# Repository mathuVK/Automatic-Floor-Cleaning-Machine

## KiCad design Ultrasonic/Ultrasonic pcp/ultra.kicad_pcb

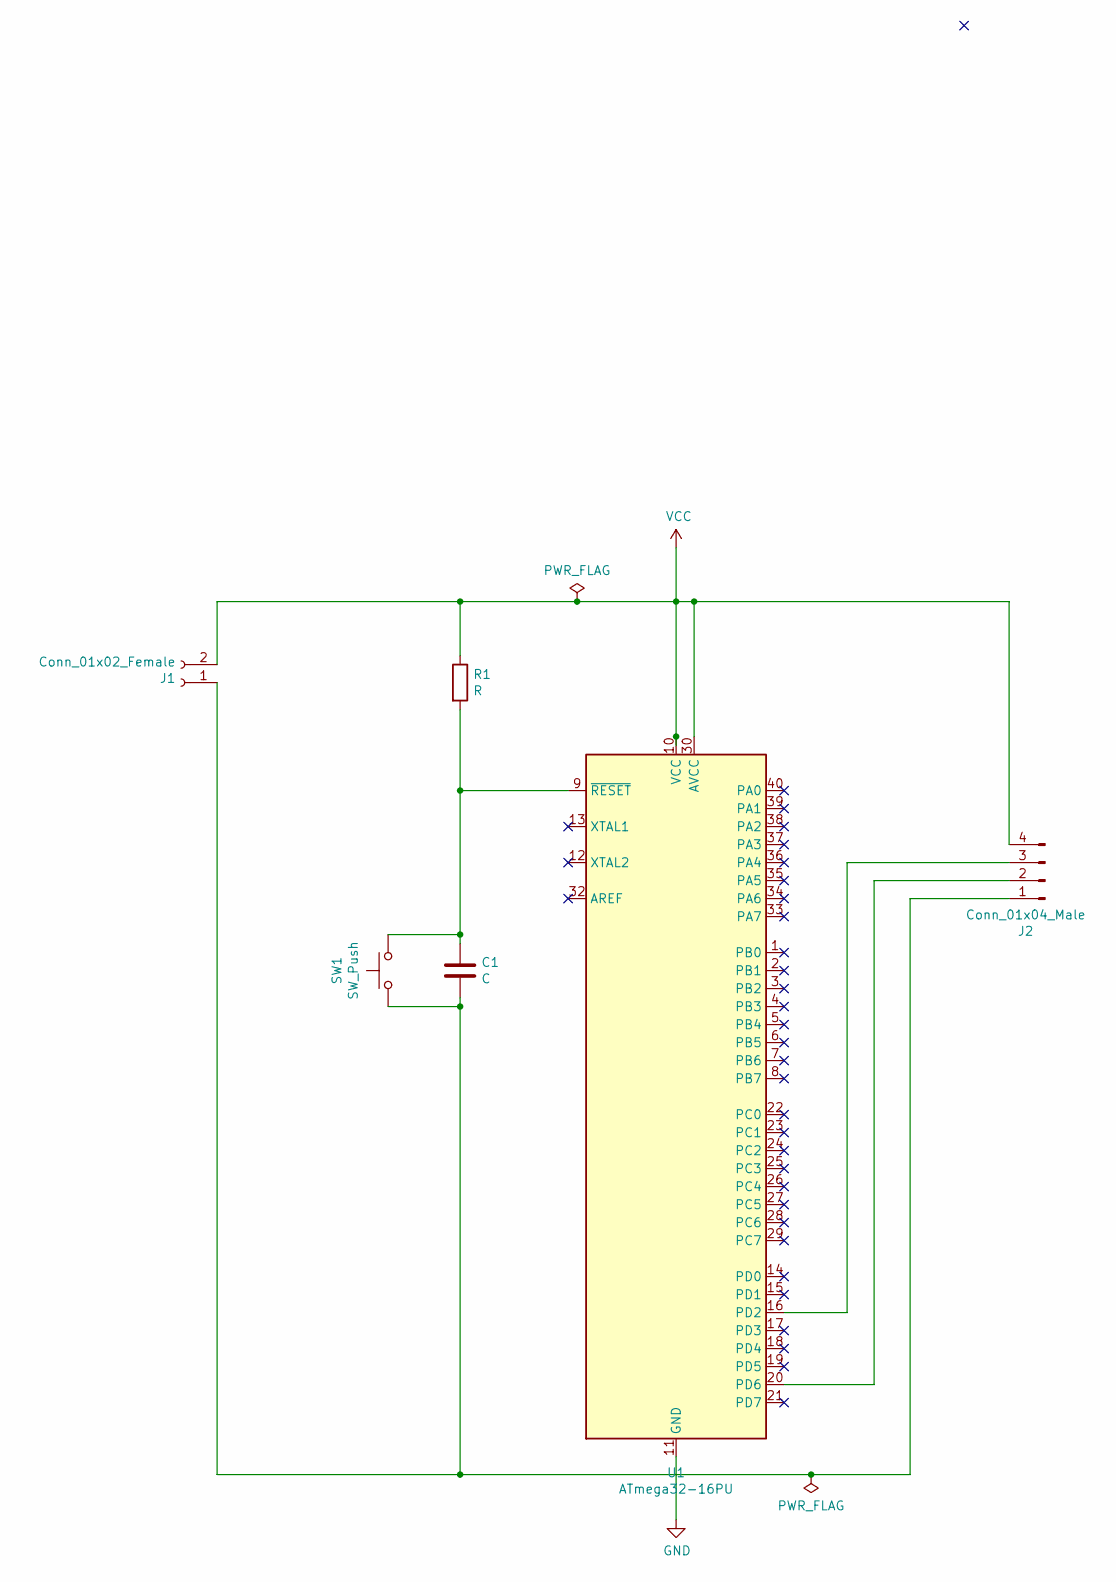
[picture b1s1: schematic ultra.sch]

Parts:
C1: C; C_Radial_D5.0mm_H7.0mm_P2.00mm
J1: Conn_01x02_Female; PinHeader_1x04_P2.54mm_Vertical
J2: Conn_01x04_Male; PinHeader_1x04_P2.54mm_Vertical
R1: R; R_Axial_DIN0207_L6.3mm_D2.5mm_P10.16mm_Horizontal
SW1: SW_Push; SW_PUSH_6mm_H5mm
U1: ATmega32-16PU; DIP-40_W15.24mm

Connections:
GND: U1.11 (GND), U1.31 (GND)
unnamed: C1.1, R1.2, SW1.2, U1.9 (~RESET)
unnamed: C1.2, J1.1, J2.1, SW1.1
unnamed: J2.2, U1.20 (PD6)
unnamed: J2.3, U1.16 (PD2)
VCC: J1.2, J2.4, R1.1, U1.10 (VCC), U1.30 (AVCC)

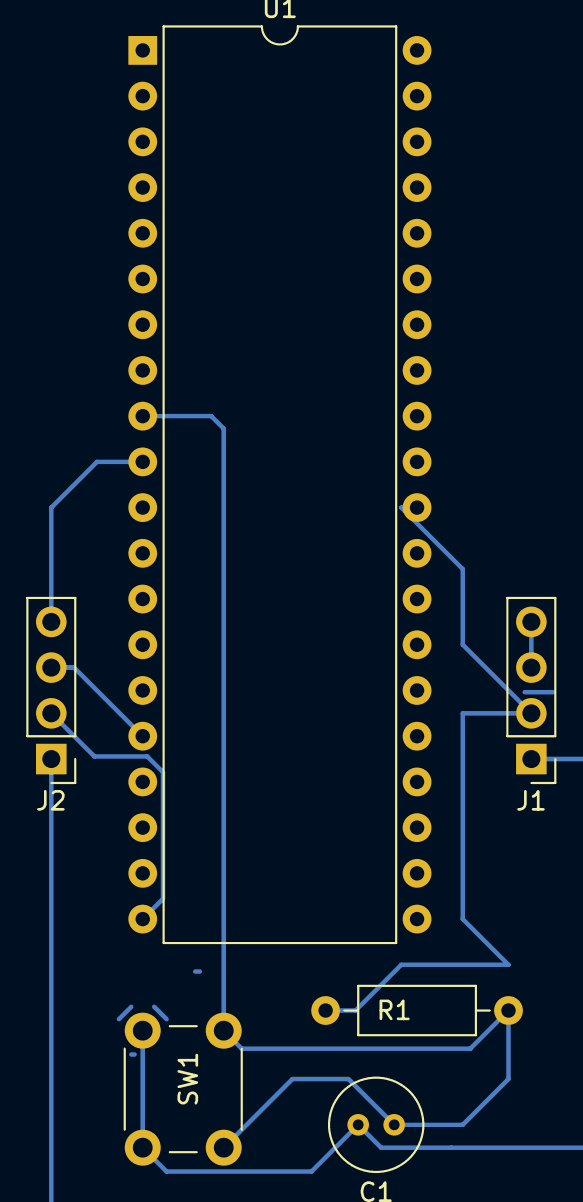
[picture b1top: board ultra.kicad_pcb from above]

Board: 2 copper layers, 6 parts (0 on the bottom side), 6 nets.

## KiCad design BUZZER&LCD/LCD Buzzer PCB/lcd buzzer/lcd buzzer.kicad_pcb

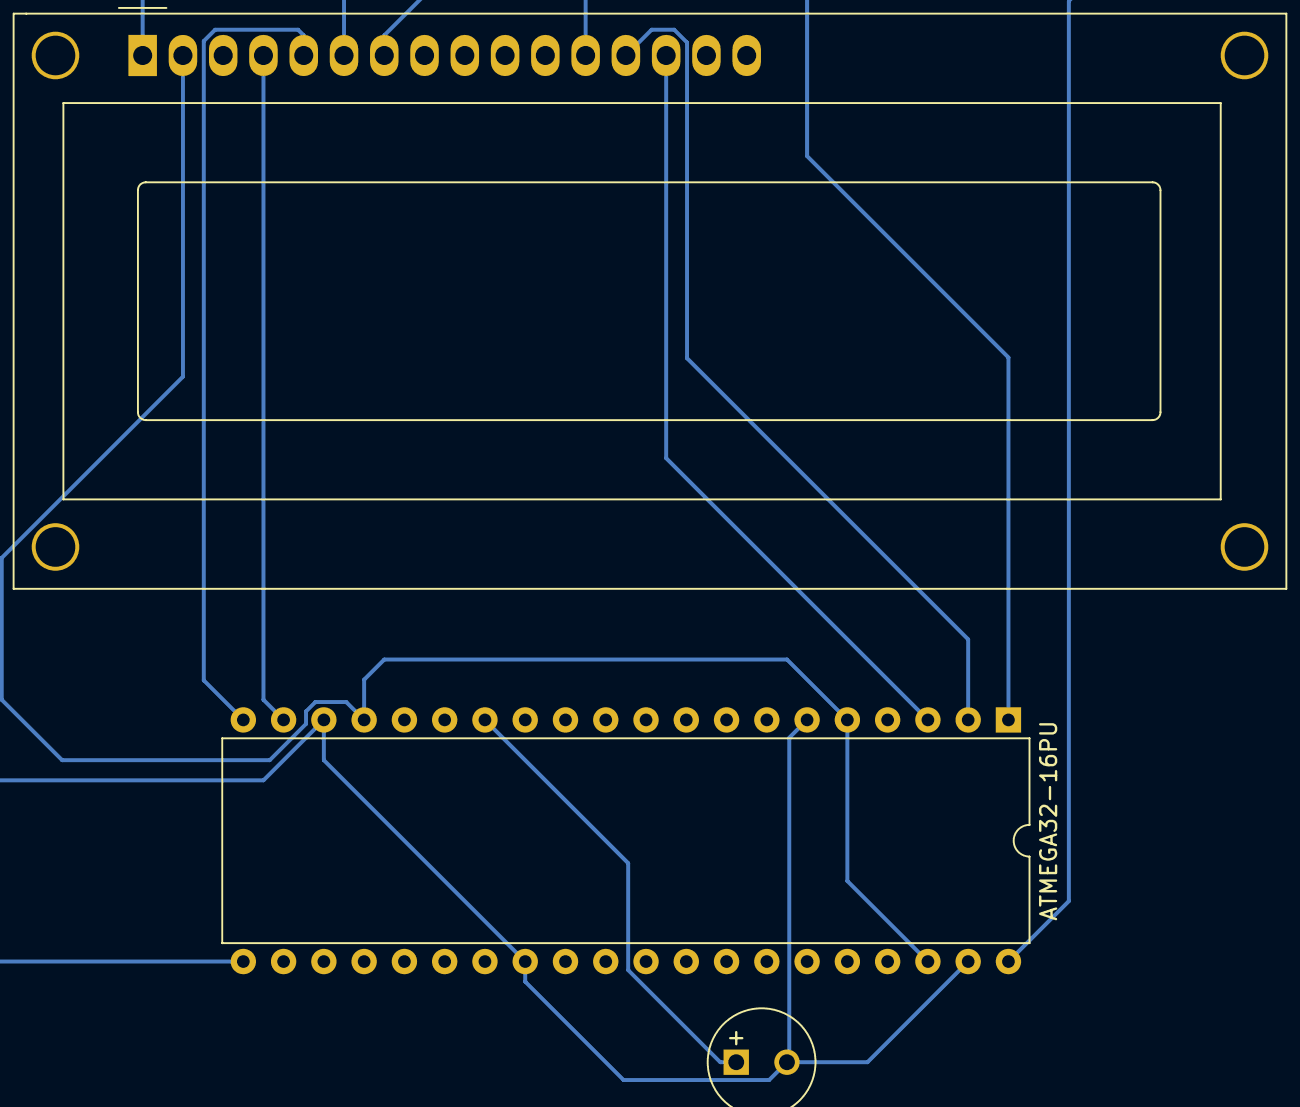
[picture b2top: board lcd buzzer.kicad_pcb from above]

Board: 2 copper layers, 3 parts (0 on the bottom side), 10 nets.

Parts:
 BUZZER: Buzzer; MagneticBuzzer_Kingstate_KCG0601
ATMEGA32-16PU: ATmega32-16AU; DIP-40_W15.24mm
LCD: WC1602A

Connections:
GND: BUZZER.2, ATMEGA32-16PU.6, ATMEGA32-16PU.18, ATMEGA32-16PU.28, ATMEGA32-16PU.39, LCD.1
unnamed: BUZZER.1, ATMEGA32-16PU.14
unnamed: ATMEGA32-16PU.19, LCD.4
unnamed: ATMEGA32-16PU.20, LCD.5
unnamed: ATMEGA32-16PU.21, LCD.6
unnamed: ATMEGA32-16PU.40, LCD.7
unnamed: ATMEGA32-16PU.1, LCD.12
unnamed: ATMEGA32-16PU.2, LCD.13
unnamed: ATMEGA32-16PU.3, LCD.14
VCC: ATMEGA32-16PU.5, ATMEGA32-16PU.17, ATMEGA32-16PU.38, LCD.2

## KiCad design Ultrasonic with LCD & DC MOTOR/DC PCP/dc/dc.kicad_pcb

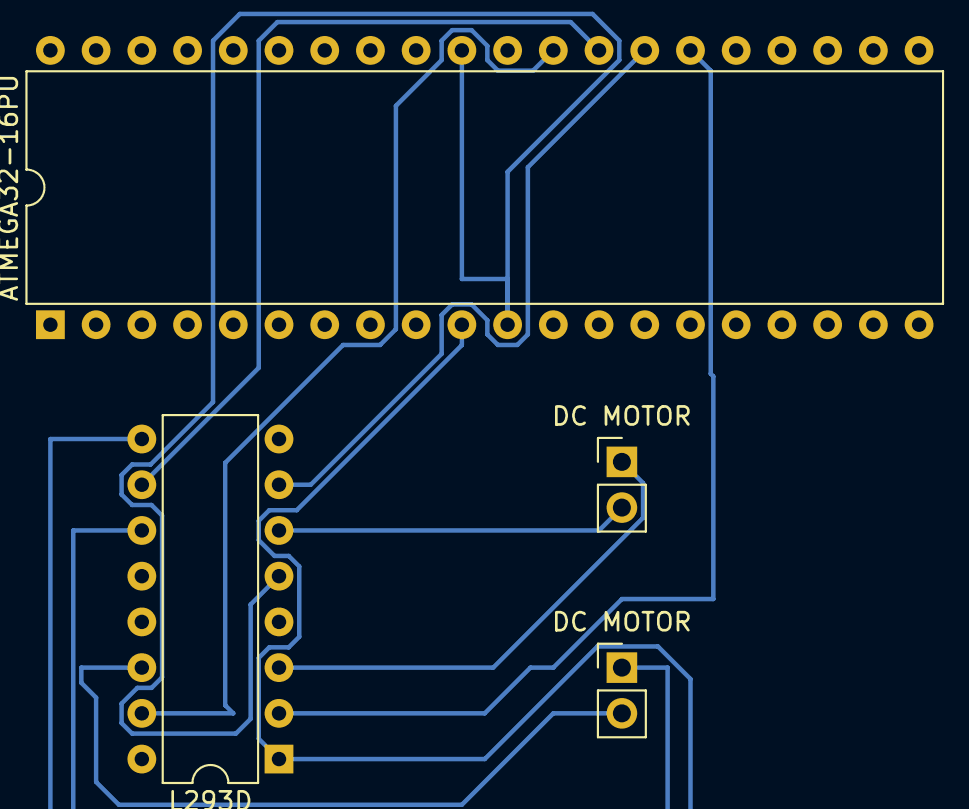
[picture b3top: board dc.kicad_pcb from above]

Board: 2 copper layers, 4 parts (0 on the bottom side), 10 nets.

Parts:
ATMEGA32-16PU: ATmega32-16PU; DIP-40_W15.24mm
DC MOTOR: Motor_DC; PinHeader_1x02_P2.54mm_Vertical
DC MOTOR#2: Motor_DC; PinHeader_1x02_P2.54mm_Vertical
L293D: L293D; DIP-16_W7.62mm

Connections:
GND: ATMEGA32-16PU.11, ATMEGA32-16PU.31, L293D.5
unnamed: DC MOTOR.1, L293D.3
unnamed: DC MOTOR.2, L293D.6
unnamed: DC MOTOR#2.1, L293D.11
unnamed: DC MOTOR#2.2, L293D.14
unnamed: ATMEGA32-16PU.26, L293D.2
unnamed: ATMEGA32-16PU.27, L293D.7
unnamed: ATMEGA32-16PU.28, L293D.10
unnamed: ATMEGA32-16PU.29, L293D.15
VCC: ATMEGA32-16PU.10, L293D.1, L293D.9

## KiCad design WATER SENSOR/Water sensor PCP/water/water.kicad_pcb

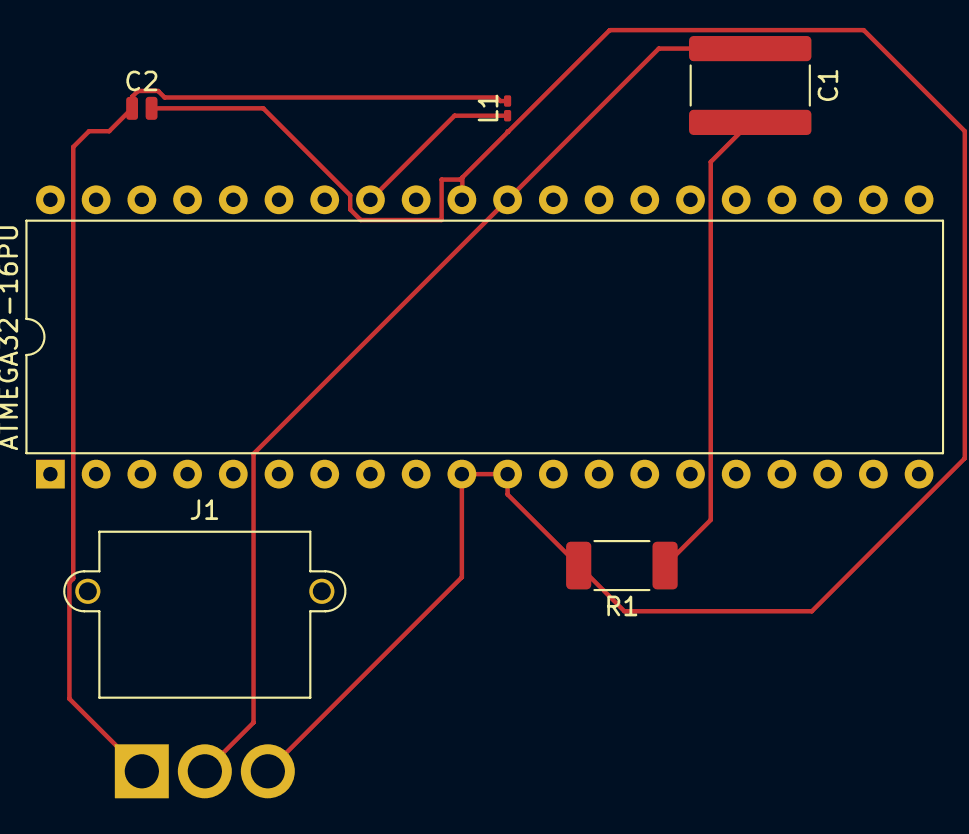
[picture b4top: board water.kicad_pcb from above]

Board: 2 copper layers, 6 parts (0 on the bottom side), 5 nets.

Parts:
ATMEGA32-16PU: ATmega32-16PU; DIP-40_W15.24mm
C1: C; C_1825_4564Metric
C2: C; C_0504_1310Metric
J1: WATER LEVELE SENSOR; AMASS_MR30PW-M_1x03_P3.50mm_Horizontal
L1: L; L_0201_0603Metric_Pad0.64x0.40mm_HandSolder
R1: R; R_2010_5025Metric_Pad1.40x2.65mm_HandSolder

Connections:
GND: ATMEGA32-16PU.30, C1.1, J1.2
unnamed: C1.2, R1.1
unnamed: C2.1, J1.1, L1.2
unnamed: ATMEGA32-16PU.33, L1.1
VCC: ATMEGA32-16PU.10, ATMEGA32-16PU.11, ATMEGA32-16PU.31, C2.2, J1.3, R1.2

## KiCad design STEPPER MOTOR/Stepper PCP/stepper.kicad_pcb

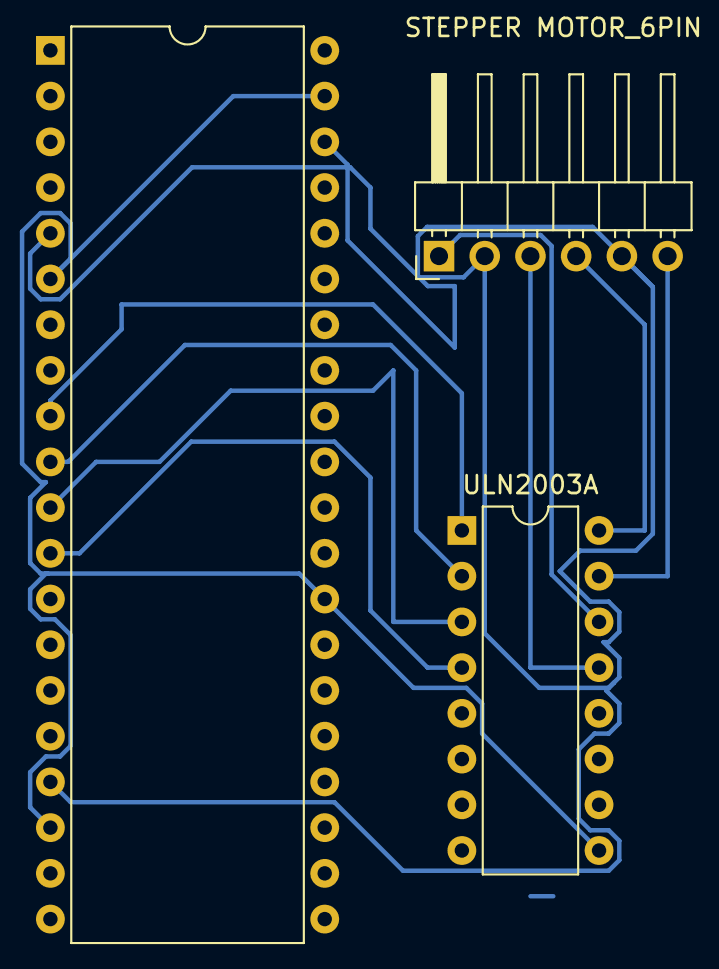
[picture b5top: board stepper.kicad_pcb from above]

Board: 2 copper layers, 3 parts (0 on the bottom side), 10 nets.

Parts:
STEPPER MOTOR_6PIN: Stepper_Motor_unipolar_6pin; PinHeader_1x06_P2.54mm_Horizontal
ULN2003A: ULN2003A; DIP-16_W7.62mm
atmega32-16AU: ATmega32-16AU; DIP-40_W15.24mm

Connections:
GND: ULN2003A.9, atmega32-16AU.6, atmega32-16AU.18, atmega32-16AU.28, atmega32-16AU.39
unnamed: STEPPER MOTOR_6PIN.1, ULN2003A.14
unnamed: STEPPER MOTOR_6PIN.3, ULN2003A.13
unnamed: STEPPER MOTOR_6PIN.4, ULN2003A.16
unnamed: STEPPER MOTOR_6PIN.6, ULN2003A.15
unnamed: ULN2003A.1, atmega32-16AU.9
unnamed: ULN2003A.2, atmega32-16AU.10
unnamed: ULN2003A.3, atmega32-16AU.11
unnamed: ULN2003A.4, atmega32-16AU.12
VCC: STEPPER MOTOR_6PIN.2, STEPPER MOTOR_6PIN.5, atmega32-16AU.5, atmega32-16AU.17, atmega32-16AU.38

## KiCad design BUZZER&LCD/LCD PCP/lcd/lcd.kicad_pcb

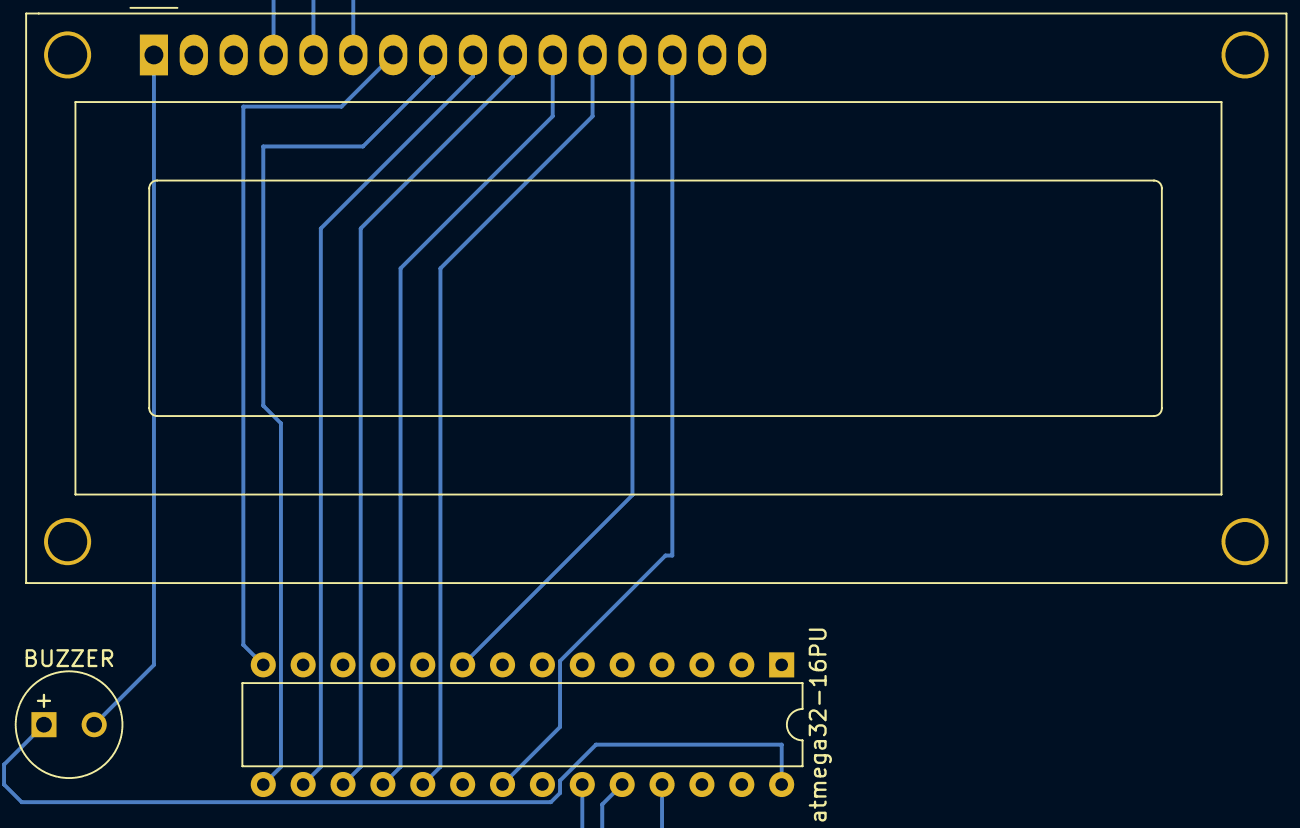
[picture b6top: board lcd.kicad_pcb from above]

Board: 2 copper layers, 3 parts (0 on the bottom side), 13 nets.

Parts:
BUZZER: Buzzer; MagneticBuzzer_Kingstate_KCG0601
LCD: WC1602A
atmega32-16PU: ATmega8-16PU; DIP-28_W7.62mm

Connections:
Earth: BUZZER.2, LCD.1
unnamed: BUZZER.1, atmega32-16PU.28
unnamed: LCD.4, atmega32-16PU.23
unnamed: LCD.5, atmega32-16PU.24
unnamed: LCD.6, atmega32-16PU.25
unnamed: LCD.7, atmega32-16PU.14
unnamed: LCD.8, atmega32-16PU.15
unnamed: LCD.9, atmega32-16PU.16
unnamed: LCD.10, atmega32-16PU.17
unnamed: LCD.11, atmega32-16PU.18
unnamed: LCD.12, atmega32-16PU.19
unnamed: LCD.13, atmega32-16PU.9
unnamed: LCD.14, atmega32-16PU.21

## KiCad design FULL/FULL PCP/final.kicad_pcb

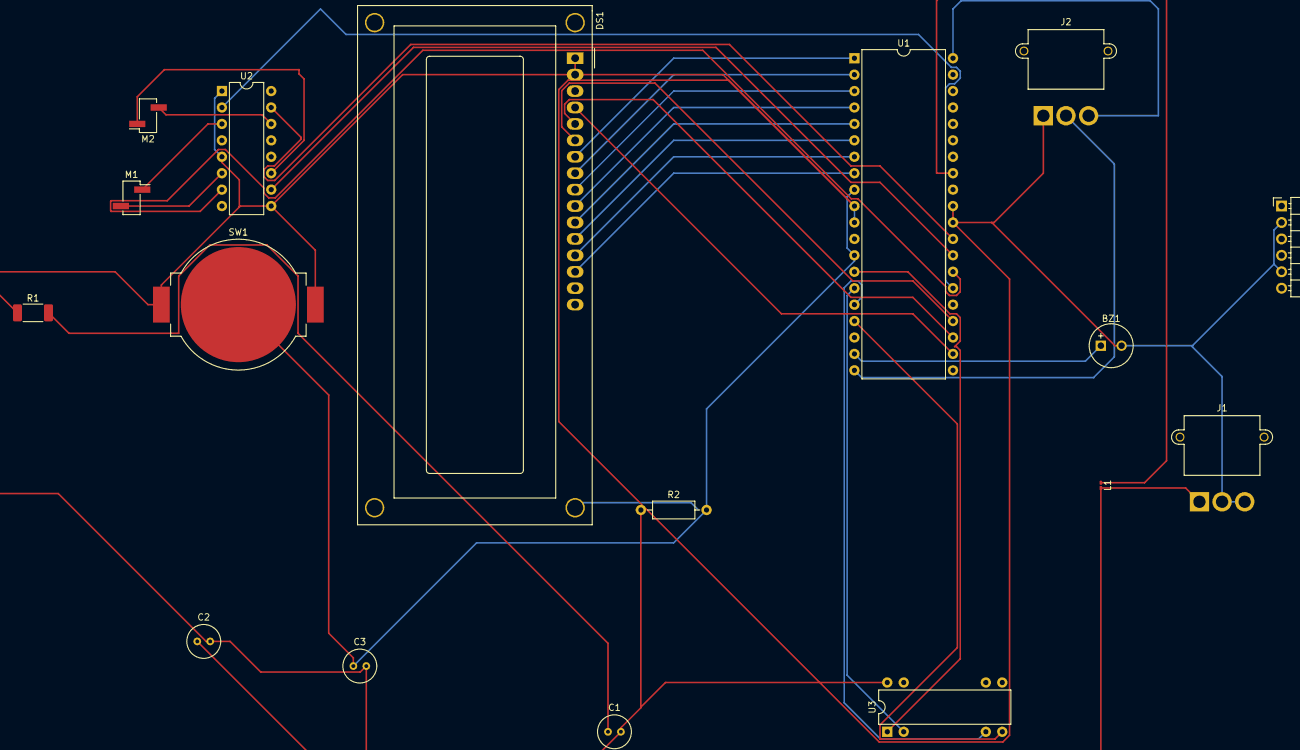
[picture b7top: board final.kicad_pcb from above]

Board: 2 copper layers, 17 parts (0 on the bottom side), 31 nets.

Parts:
BZ1: Buzzer; MagneticBuzzer_Kingstate_KCG0601
C1, C2, C3: C; C_Radial_D5.0mm_H7.0mm_P2.00mm
DS1: WC1602A
J1: Conn_01x03_Male; AMASS_MR30PW-M_1x03_P3.50mm_Horizontal
J2: Conn_01x04_Male; AMASS_MR30PW-M_1x03_P3.50mm_Horizontal
L1: L; L_0201_0603Metric_Pad0.64x0.40mm_HandSolder
M1, M2: Motor_AC; PinHeader_1x02_P2.54mm_Vertical_SMD_Pin1Right
M3: Stepper_Motor_unipolar_6pin; PinHeader_1x06_P2.54mm_Horizontal
R1: R; R_2010_5025Metric_Pad1.40x2.65mm_HandSolder
R2: R; R_Axial_DIN0207_L6.3mm_D2.5mm_P10.16mm_Horizontal
SW1: SW_Push; BatteryHolder_MPD_BC2003_1x2032
U1: ATmega32-16PU; DIP-40_W15.24mm
U2: L293D; DIP-16_W7.62mm
U3: ULN2003A; DIP-8-16_W7.62mm

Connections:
GND: BZ1.2, C1.2, C2.2, C3.2, DS1.1, DS1.2, J1.2, J1.3, J2.1, M3.2, M3.5, R1.1, R2.1, SW1.1, U1.10, U1.11, U1.30, U1.31, U2.1, U2.5, U2.9, U3.8
unnamed: BZ1.1, U1.19
unnamed: C1.1, R1.2
unnamed: C2.1, J1.1, L1.2
unnamed: C3.1, R2.2, SW1.2, U1.9, U1.13
unnamed: DS1.4, U1.22
unnamed: DS1.5, U1.23
unnamed: DS1.6, U1.24
unnamed: DS1.7, U1.1
unnamed: DS1.8, U1.2
unnamed: DS1.9, U1.3
unnamed: DS1.10, U1.4
unnamed: DS1.11, U1.5
unnamed: DS1.12, U1.6
unnamed: DS1.13, U1.7
unnamed: DS1.14, U1.8
unnamed: J2.2, U1.20
unnamed: J2.3, U1.40
unnamed: L1.1, U1.33
unnamed: M1.1, U2.3
unnamed: M1.2, U2.6
unnamed: M2.1, U2.11
unnamed: M2.2, U2.14
unnamed: U1.14, U3.1
unnamed: U1.15, U3.2
unnamed: U1.16, U3.3
unnamed: U1.17, U3.4
unnamed: U1.26, U2.2
unnamed: U1.27, U2.7
unnamed: U1.28, U2.10
unnamed: U1.29, U2.15
